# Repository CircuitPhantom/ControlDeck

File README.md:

# ControlDeck

A compact, open-source desktop media controller / macropad, built for the **StarDance Hackpad** mission on [Hack Club](https://hackclub.com/).

3 mechanical keys + a rotary encoder with push-button, all driven by a Seeeduino XIAO RP2040 running QMK firmware.

## Important Note

I haven't tested it myself yet, so no guarantees it works 100%. I plan to build it this month (August 2026) but if you end up building it before I do, let me know how it goes!

## Quick Start

1. **Order the PCB** — send the files in [`/pcb`](./pcb) to your fab of choice (e.g. JLCPCB).
2. **Print the case** — slice and print the enclosure files in [`/cad`](./cad).
3. **Flash the firmware** — build and flash with QMK:
   ```bash
   qmk compile -kb controldeck -km default
   qmk flash -kb controldeck -km default
   ```
   See [`firmware/controldeck/readme.md`](./firmware/controldeck/readme.md) for full build/flash instructions.
4. **Assemble** — solder the switches and encoder per the [wiring table](#wiring) below, mount in the case.

## Features

- 3x Cherry MX-style mechanical switches (media/macro keys)
- 1x EC11 rotary encoder with push switch (volume control / scroll / custom actions)
- Custom PCB designed in KiCad
- 3D-printed enclosure designed in Fusion 360
- Powered by a Seeeduino XIAO RP2040 running QMK firmware

## Hardware

| Component                              | Qty | Notes                         |
| --------------------------------------- | --- | ------------------------------ |
| Seeeduino XIAO RP2040                   | 1   | Main controller                |
| Cherry MX-style keyswitch               | 3   | SW1, SW2, SW3                  |
| EC11 rotary encoder (with push switch)  | 1   | SW6                            |
| Custom PCB                              | 1   | KiCad design, see `/pcb`       |
| 3D-printed case (top + base)            | 1   | Fusion 360 design, see `/cad`  |

### Wiring

All switches share a common GND. Signal pins connect to the XIAO RP2040 as follows:

| Pin | Function                       |
| --- | ------------------------------- |
| GND | Common ground for all switches  |
| D1  | Encoder A                       |
| D2  | Encoder B                       |
| D3  | Encoder push switch             |
| D4  | SW1                              |
| D5  | SW2                              |
| D6  | SW3                              |

## Firmware

Built with [QMK Firmware](https://qmk.fm/) for RP2040, using `DIRECT_PINS` (no key matrix) and the built-in QMK encoder support. See `firmware/controldeck/readme.md` for build/flash instructions.

## 3D Models Used

- Cherry MX keyswitches — [GrabCAD](https://grabcad.com/library/cherry-mx-switches-mx-1) *(not redistributed in this repo — download from source, see License section)*
- EC11 rotary encoder — [GrabCAD](https://grabcad.com/library/rotary-encoder-17) *(not redistributed in this repo — download from source, see License section)*
- Cherry MX keycaps — [hineybush/CherryMX](https://github.com/hineybush/CherryMX) (MIT License)
- XIAO RP2040 — [Seeed Studio Wiki](https://wiki.seeedstudio.com/XIAO-RP2040/) (reference only, no files redistributed)

## Project Structure

```
├── cad/        # STEP file for the enclosure
├── firmware/
|    └──controldeck    # QMK files for the firmware
├── pcb/       # PCB schematic and layout
├── production/  # Production ready files
├── Demo.mp4
├── LICENSE
└── README.md
```

## About

Built by CircuitPhantom for the StarDance Hackpad mission on Hack Club.

## Gallery

## License

The hardware design (PCB, KiCad files), original enclosure design, and this repository's own content are licensed under the **MIT License** — see [`LICENSE`](./LICENSE). Feel free to fork, remix, and build your own.

**Third-party and per-file exceptions — not covered by the MIT license above:**

| Asset | Source | License / Terms |
|---|---|---|
| Cherry MX keyswitch 3D model | [GrabCAD](https://grabcad.com/library/cherry-mx-switches-mx-1) | GrabCAD Library content — personal/non-commercial use only; contact the original uploader for redistribution or commercial use. **Not redistributed in this repo.** |
| EC11 rotary encoder 3D model | [GrabCAD](https://grabcad.com/library/rotary-encoder-17) | Same as above — GrabCAD non-commercial terms. **Not redistributed in this repo.** |
| Cherry MX keycap models | [hineybush/CherryMX](https://github.com/hineybush/CherryMX) | MIT License (original author: Josh Hinnebusch) |
| `firmware/controldeck/keymaps/default/keymap.c` | QMK `new-keyboard` template | **GPL-2.0-or-later**, per the file's own header (`SPDX-License-Identifier: GPL-2.0-or-later`) — this specific file is not covered by this repo's MIT license |
| `firmware/controldeck/keyboard.json`, `firmware/controldeck/readme.md` | Original, written for this project | MIT (this repo's license) |
| XIAO RP2040 reference | [Seeed Studio Wiki](https://wiki.seeedstudio.com/XIAO-RP2040/) | Documentation reference only, no files redistributed. |

If you plan to redistribute this project (including the `cad/` STL files), make sure any GrabCAD-sourced geometry is either removed/regenerated or that you've obtained permission from the original uploader — the MIT license on this repo does not extend to that content. Likewise, `keymap.c` remains GPL-2.0-or-later regardless of the repo-level MIT license.

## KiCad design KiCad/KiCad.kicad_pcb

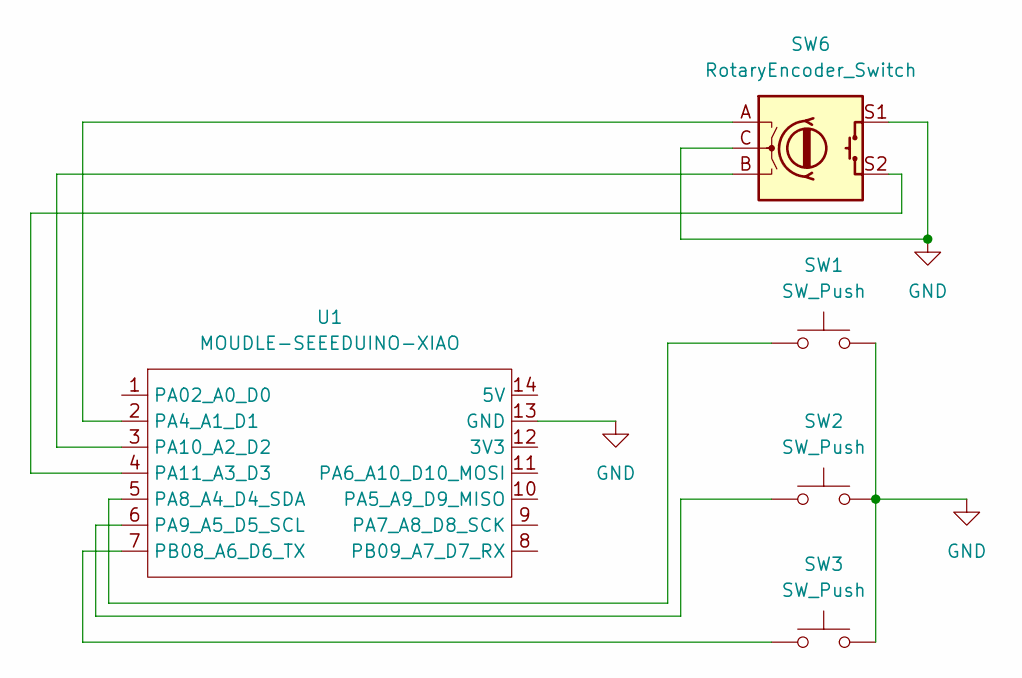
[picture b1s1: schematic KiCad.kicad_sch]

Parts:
SW1, SW2, SW3: SW_Push; SW_Cherry_MX_1.00u_PCB
SW6: RotaryEncoder_Switch; RotaryEncoder_Alps_EC11E-Switch_Vertical_H20mm_MountingHoles
U1: MOUDLE-SEEEDUINO-XIAO; XIAO-Generic-Hybrid-14P-2.54-21X17.8MM

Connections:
GND: SW1.2, SW2.2, SW3.2, SW6.C, SW6.S1, U1.13 (GND)
unnamed: SW6.A, U1.2 (PA4_A1_D1)
unnamed: SW1.1, U1.5 (PA8_A4_D4_SDA)
unnamed: SW2.1, U1.6 (PA9_A5_D5_SCL)
unnamed: SW6.B, U1.3 (PA10_A2_D2)
unnamed: SW6.S2, U1.4 (PA11_A3_D3)
unnamed: SW3.1, U1.7 (PB08_A6_D6_TX)

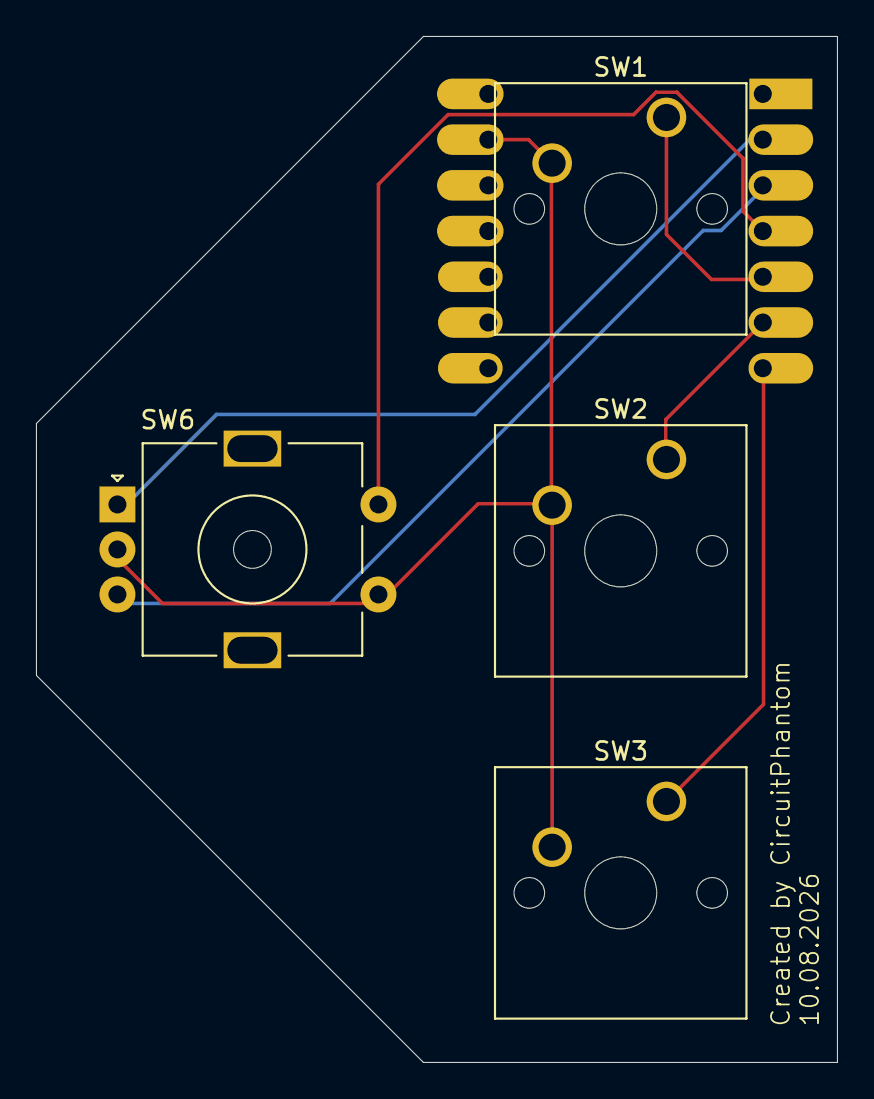
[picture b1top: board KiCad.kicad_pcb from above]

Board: 2 copper layers, 44.5 x 57.0 mm, 5 parts (1 on the bottom side), 7 nets.
